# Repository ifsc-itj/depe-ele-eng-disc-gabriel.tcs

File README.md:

# template-discente-10-fases
Template para repositório de alunos para cursos com 10 fases

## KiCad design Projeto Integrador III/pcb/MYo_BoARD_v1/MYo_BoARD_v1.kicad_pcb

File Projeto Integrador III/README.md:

# MYo_BoARD
---
<p style="text-align: justify;">
Projeto de uma placa de aquisição de sinais biomédicos  de 3 canais desenvolvida na disciplina de Projeto Integrador III do curso de Engenharia Elétrica do IFSC-Itajaí.
</p>

---
## Sumário

- [MYo\_BoARD](#myo_board)
  - [Sumário](#sumário)
  - [Introdução](#introdução)
    - [Os biossinais](#os-biossinais)
    - [Fluxograma do sistema](#fluxograma-do-sistema)
  - [Ensaio de frequência nos amplificadores - *AC Sweep*](#ensaio-de-frequência-nos-amplificadores---ac-sweep)
  - [Projeto do circuito de aquisição](#projeto-do-circuito-de-aquisição)
    - [Filtro Notch](#filtro-notch)
    - [Pré-amplificação](#pré-amplificação)
    - [Filtro passa-baixas](#filtro-passa-baixas)
    - [Ganho e *Offset*](#ganho-e-offset)
  - [Circuito Completo (v2)](#circuito-completo-v2)
  - [ESP-32 S3 - Características de Interesse](#esp-32-s3---características-de-interesse)
  - [Plataforma de Aquisição (MYo\_GRaPH)](#plataforma-de-aquisição-myo_graph)
    - [Interface Inicial](#interface-inicial)
    - [Interface Final](#interface-final)

---
## Introdução
### Os biossinais

<p style="text-align: justify;">
Os biossinais são manifestações elétricas geradas pela atividade fisiológica dos tecidos e órgãos do corpo humano. Entre os mais estudados e aplicados em sistemas de aquisição e análise estão o eletroencefalograma (EEG), o eletrocardiograma (ECG) e o eletromiograma (EMG). Esses sinais carregam informações valiosas sobre o funcionamento do sistema nervoso, do coração e dos músculos esqueléticos, sendo amplamente utilizados em diagnósticos médicos, controle de próteses, interfaces cérebro-máquina e em pesquisas na área biomédica.
</p>

<p style="text-align: justify;">
O sinal de EEG reflete a atividade elétrica cerebral, caracterizado por amplitudes muito baixas (na ordem de microvolts) e frequências relativamente baixas (até cerca de 100 Hz). Devido à sua suscetibilidade a ruídos e interferências, sua captação exige alto grau de amplificação e filtragem. É amplamente utilizado em estudos de sono, epilepsia e monitoramento do estado cognitivo.
</p>

<p style="text-align: justify;">
Já o ECG registra a atividade elétrica do coração durante o ciclo cardíaco. Suas amplitudes são mais elevadas do que as do EEG e suas frequências se concentram nas faixas de até 150 Hz. O ECG é essencial no diagnóstico de arritmias, infartos e outras condições cardíacas, sendo um dos exames biomédicos mais comuns.
</p>

<p style="text-align: justify;">
O EMG, por sua vez, capta a atividade elétrica dos músculos esqueléticos, resultante da ativação das fibras musculares pelo sistema nervoso. O sinal mioelétrico é caracterizado por amplitudes maiores (até milivolts) e uma banda de frequência que pode variar entre 20 Hz e 5000 Hz, dependendo do tipo de contração muscular e do músculo analisado. Este sinal é de particular interesse em aplicações de reabilitação, controle de próteses ativas e em sistemas de interação homem-máquina.
</p>

<table>
<thead>
  <tr>
    <th style="text-align:center">Biossinal</th>
    <th style="text-align:center">Faixa de Frequência (Hz)</th>
    <th style="text-align:center">Amplitude Típica</th>
  </tr>
</thead>
<tbody>
  <tr>
    <td style="text-align:center">EEG</td>
    <td style="text-align:center">0,5 – 100</td>
    <td style="text-align:center">10 – 100 µV</td>
  </tr>
  <tr>
    <td style="text-align:center">ECG</td>
    <td style="text-align:center">0,05 – 150</td>
    <td style="text-align:center">0,5 – 4 mV</td>
  </tr>
  <tr>
    <td style="text-align:center">EMG</td>
    <td style="text-align:center">20 – 5000 (típico até 500)</td>
    <td style="text-align:center">50 µV – 5 mV</td>
  </tr>
</tbody>
</table>

### Fluxograma do sistema

O sistema foi desenvolvido conforme os fluxogramas a seguir.

| <br><em>Fluxograma da versão com filtro Notch e alimentação simétrica (v1).</em> |
|:--:|

| <br><em>Fluxograma da versão sem filtro Notch e alimentação assimétrica (v2).</em> |
|:--:|

## Ensaio de frequência nos amplificadores - *AC Sweep*

<p style="text-align: justify;">
A fim de verificar a resposta em frequência dos amplificadores de instrumentação, realizou-se um ensaio que consiste em variar a frequência do sinal de entrada e medir o sinal na saída do amplificador. Dessa maneira, é possível obter um gráfico que descreve a variação do ganho em função do aumento da frequência a partir dos valores de entrada e saída medidos. O circuito para ensaio dos amplificadores foram montados conforme recomendação do <em>datasheet</em> de cada um deles (vide Figura 1). Tanto o INA128 e o AD623 possuem a mesma configuração de pinos e, portanto, utilizou-se o mesmo circuito para ambos, diferenciando apenas no valor dos resistores de ganho. A resposta de cada amplificador consta na Figura 2. Os equipamentos utilizados para esse ensaio foram: osciloscópio digital e gerador de funções, ambos disponibilizados pelo <em>campus</em>.
</p>

| <br><em>Figura 1 – Circuito AC Sweep</em> |
|:--:|

| <br><em>Figura 2 – Resposta em frequência dos amplificadores</em> |
|:--:|

## Projeto do circuito de aquisição
### Filtro Notch

<p style="text-align: justify;">
O primeiro estágio do circuito consiste em um filtro que remova sinais de frequência de 60 Hz a fim de evitar interferências ruidosas oriundas da rede. Para tal filtro, utilizou-se a topologia Duplo-T, a qual permite selecionar a frequência central e o fator de qualidade de forma independente. O circuito obtido e a sua respectiva resposta constam nas Figuras 3 e 4, respectivamente. A Figura 5 mostra a resposta do circuito já montado e testado em bancada.
</p>

| <br><em>Figura 3 – Circuito do Filtro Notch</em> |
|:--:|

| <br><em>Figura 4 – Resposta em frequência do filtro Notch (Simulado)</em> |
|:--:|

| <br><em>Figura 5 – Resposta em frequência do filtro Notch (Real)</em> |
|:--:|

### Pré-amplificação

<p style="text-align: justify;">
O segundo estágio consiste em um amplificador de instrumentação que mitiga o ruído de modo comum (<em>CMRR</em>) do sinal diferencial. Portanto, o ganho nesse estágio pode ser mais baixo, optando-se, então, por dar um maior ganho em estágios posteriores. Devido a banda de passagem do AD623AN ser mais linear que a do INA128P, optou-se por utilizá-lo no circuito dessa etapa. O circuito utilizado nessa etapa é o mesmo da Figura 1, o qual é o recomendado pelo fabricante no <em>datasheet</em>
</p>

### Filtro passa-baixas

<p style="text-align: justify;">
O terceiro estágio consiste em um filtro passa-baixas de segunda ordem, topologia Sallen-Key. Esse filtro possui frequência de corte em 1 kHz. O circuito utilizado foi o da Figura 6. A Figura 7 Mostra a resposta em frequência obtida para o circuito em simulação.
</p>

| <br><em>Figura 6 – Circuito do filtro passa-baixas</em> |
|:--:|

| <br><em>Figura 7 – Resposta em frequência do filtro Passa-baixas (Simulado)</em> |
|:--:|

### Ganho e *Offset*

<p style="text-align: justify;">
Nessa etapa, o sinal é condicionado dentro dos limites de operação do ESP-32 S3. É dado um ganho variável de 1 à 201 e um deslocamento de tensão DC de, aproximadamente, 1,65 V.
</p>

## Circuito Completo (v2)

<p style="text-align: justify;">
Dado às necessidades de condicionamento do sinal serem cruciais à esse projeto e à algumas dificuldades encontradas durante a montagem e testes do circuito em <em>protoboard</em>, optou-se por não utilizar o filtro Notch (Duplo-T) devido ao mesmo exigir uma alimentaçã simétrica, o que trouxe dificuldades na montagem e teste em bancada, inviabilizando, então, a validação de seu funcionamento. Com isso, utilizou-se uma configuração já conhecida e validada em projetos anteriores com alimentação simétrica, mas sem o filtro analógico Notch. O esquemátio do circuito completo e o layout da placa de circuito impresso (PCI) constam nas figuras abaixo.
</p>

| <br><em>Circuito Completo (v2)</em> |
|:--:|

| <br><em>Visão Superior da PCI</em> |
|:--:|

| <br><em>Visão Inferior da PCI</em> |
|:--:|

<p style="text-align: justify;">
A ideia final do projeto é que as placas sejam módulos independentes que podem ser concatenados, formando uma rede de aquisição de multiplos canais, a depender da aplicação e da capacidade do microcontrolador adotado para o projeto. No presente projeto a proposta são 3 canais de aquisição e a utilização do ESP-32 S3.
</p>

## ESP-32 S3 - Características de Interesse

| Parâmetro                          | Valor                                                                                                             |
| ---------------------------------- | ----------------------------------------------------------------------------------------------------------------- |
| **Canalização ADC**                | 2 × SAR ADC de 12 bits, até 20 canais (ADC1\_CH0…CH9 disponíveis com Wi-Fi; ADC2 indisponível quando Wi-Fi ativo) |
| **Taxa máxima de amostragem**      | 100 kSPS (100 000 samples/s)                                                                                      |
| **Taxa efetiva por canal**         | ≈ 33 kSPS por canal (100 kSPS ÷ 3)                                                                                |
| **Tempo de conversão**             | ≈ 10 µs (1 / 100 kSPS)                                                                                            |
| **Faixa de tensão de entrada**     | –0.3 … +3.6 V                                                                                                     |
| **Memória interna**                | ROM: 384 KB<br>SRAM: 512 KB<br>RTC SRAM: 16 KB                                                                    |
| **Recomendação de desacoplamento** | 100 nF no pino ADC para redução de ruído                                                                          |
| **Suporte a DMA**                  | Sim, via GDMA (periférico ADC mapeado com DMA)                                                                    |
| **Restrições com Wi-Fi**           | ADC2 indisponível quando Wi-Fi ativo (usar ADC1 para amostragem contínua)                                    |

## Plataforma de Aquisição (MYo_GRaPH)

### Interface Inicial
<p style="text-align: justify;">
Para o desenvolvimento da interface, foi utilizado a linguagem Python. A dependências utilizadas constam no arquivo <code>MYo_GRaPH\v1\requirements.txt</code>. Crie um ambiente de virtual e instale as dependências utilizando o gerenciador de pacotes: <code>pip install -r requirements.txt</code>.

As telas da interface inicial constam nas figuras abaixo, onde:
</p>

| Botão    | Função                                                           |
|----------|------------------------------------------------------------------|
| Start    | Inicia a leitura via porta serial                                |
| Stop     | Interrompe a leitura via porta serial                            |
| Duration | Determina o tempo de aquisição do sinal para gravação            |
| Record   | Inicia a gravação dos 3 canais e salva em arquivos *.wav* distintos |

| <br><em>Janela principal</em> |
|:--:|

| <br><em>Janela principal (Start ativado)</em> |
|:--:|

| <br><em>Janela de visualização de sinal gravado (sinal simulado)</em> |
|:--:|

### Interface Final
<p style="text-align: justify;">
Na interface final, foram adicionadas as funções de abrir arquivos <em>.wav</em> por meio do menu <code>File > Open File</code>; remover o nível DC do sinal; e selecionar a quantidade de canais a serem exibidos. Adicionou-se também a aquisição e conversão do sinal com ESP-32 S3 e amostragem do sinal via porta Serial com Python.
</p>

<p style="text-align: justify;">
A tela da interface final consta na figura abaixo, onde:
</p>

| Botão    | Função                                                           |
|----------|------------------------------------------------------------------|
| Start    | Inicia a leitura via porta serial                                |
| Stop     | Interrompe a leitura via porta serial                            |
| Duration | Determina o tempo de aquisição do sinal para gravação (não implementado)            |
| Record   | Inicia a gravação dos 3 canais e salva em arquivos *.wav* distintos (não implementado) |
| Remove DC   | Quando selecionado, remove o nivel DC do sinal |
| Canais   | Seleciona a quantidade de canais para leitura |
| Dark Mode/Light Mode   | Alterna entre modo claro e escuro na exibição do gráfico |

| <br><em>Janela de visualização de sinal em "tempo real" (sinal oriundo do gerador de funções)</em> |
|:--:|

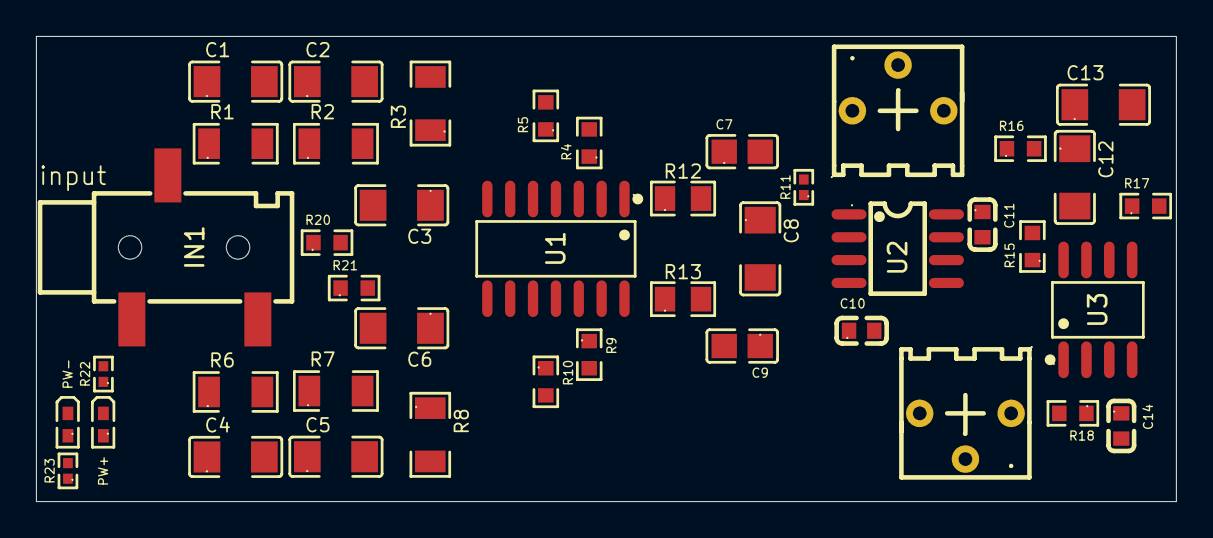
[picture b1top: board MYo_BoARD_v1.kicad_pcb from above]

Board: 2 copper layers, 63.3 x 25.8 mm, 43 parts (0 on the bottom side), 32 nets, no tracks yet.

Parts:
C1, C2, C4, C5, C13: 20n; C1206
C3, C6: 39n; C1206
C7, C9: 1n; C0805
C8: 47n; C1206
C10, C11, C14: 10u; C0603
C12: 10n; C1206
D1: PW+; LED0402-R-RD_RED
D2: PW-; LED0402-R-RD_RED
IN1: AUDIO-SMD_PJ-320B
R1, R2, R6, R7: 133k; R1206
R3, R8: 66.5k; R1206
R4, R9, R17, R18: 100R; R0603
R5, R10: 3.9k; R0603
R11: 5.23k; R0402
R12, R13: 4.02k; R0805
R14, R19: 3362P-1-203LF; RES-ADJ-TH_3362P
R15, R16, R20, R21: 10k; R0603
R22, R23: 330R; R0402
U1: TLC2274AIDR; SOIC-14_L8.7-W3.9-P1.27-LS6.0-BL
U2: AD623ARZ-R7; SOIC-8_L5.0-W4.0-P1.27-LS6.0-BL
U3: TLC2272AIDR; SOIC-8_L4.9-W3.9-P1.27-LS6.0-BL

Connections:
unnamed: C1.1, IN1.2, R1.1
unnamed: C1.2, C2.1, R3.2
unnamed: C3.2, R1.2, R2.1
unnamed: C4.1, IN1.3, R6.1
unnamed: C4.2, C5.1, R8.2
unnamed: C6.2, R6.2, R7.1
unnamed: C13.1, R15.2, R16.1
unnamed: D1.2 (A), R22.2
unnamed: D2.1 (K), R23.2
unnamed: R11.2, R14.1
unnamed: R18.2, R19.1
unnamed: C2.2, R2.2, U1.3 (IN1+)
unnamed: R4.1, R12.1, U1.1 (OUT1), U1.2 (IN1-)
unnamed: R4.2, R5.1, U1.5 (IN2+)
unnamed: C3.1, R3.1, U1.6 (IN2-), U1.7 (OUT2)
unnamed: C5.2, R7.2, U1.10 (IN3+)
unnamed: R9.1, R13.1, U1.8 (OUT3), U1.9 (IN3-)
unnamed: R9.2, R10.1, U1.12 (IN4+)
unnamed: C6.1, R8.1, U1.13 (IN4-), U1.14 (OUT4)
unnamed: C8.2, C9.1, R13.2, U2.3 (+IN)
unnamed: R14.2, U2.8 (+RG)
unnamed: C7.2, C8.1, R12.2, U2.2 (-IN)
unnamed: R11.1, U2.1 (-RG)
unnamed: R15.1, U2.6 (OUTPUT)
unnamed: C13.2, R17.1, U3.5 (IN2+), U3.7 (OUT2)
unnamed: C12.1, R16.2, U3.6 (IN2-)
unnamed: R17.2, R18.1, U3.2 (IN1-)
unnamed: R19.2, U3.1 (OUT1)
gnd: C7.1, C9.2, C10.2, C11.1, C12.2, C14.2, D1.1 (K), D2.2 (A), IN1.1, R5.2, R10.2, R21.2, U2.5 (REF)
v+: C11.2, R20.1, R22.1, U1.4 (VDD+), U2.7 (+VS), U3.8 (VDD+)
v-: C10.1, R23.1, U1.11 (VDD-), U2.4 (-VS), U3.4 (VDD-GND)
vcc/2: C14.1, R20.2, R21.1, U3.3 (IN1+)

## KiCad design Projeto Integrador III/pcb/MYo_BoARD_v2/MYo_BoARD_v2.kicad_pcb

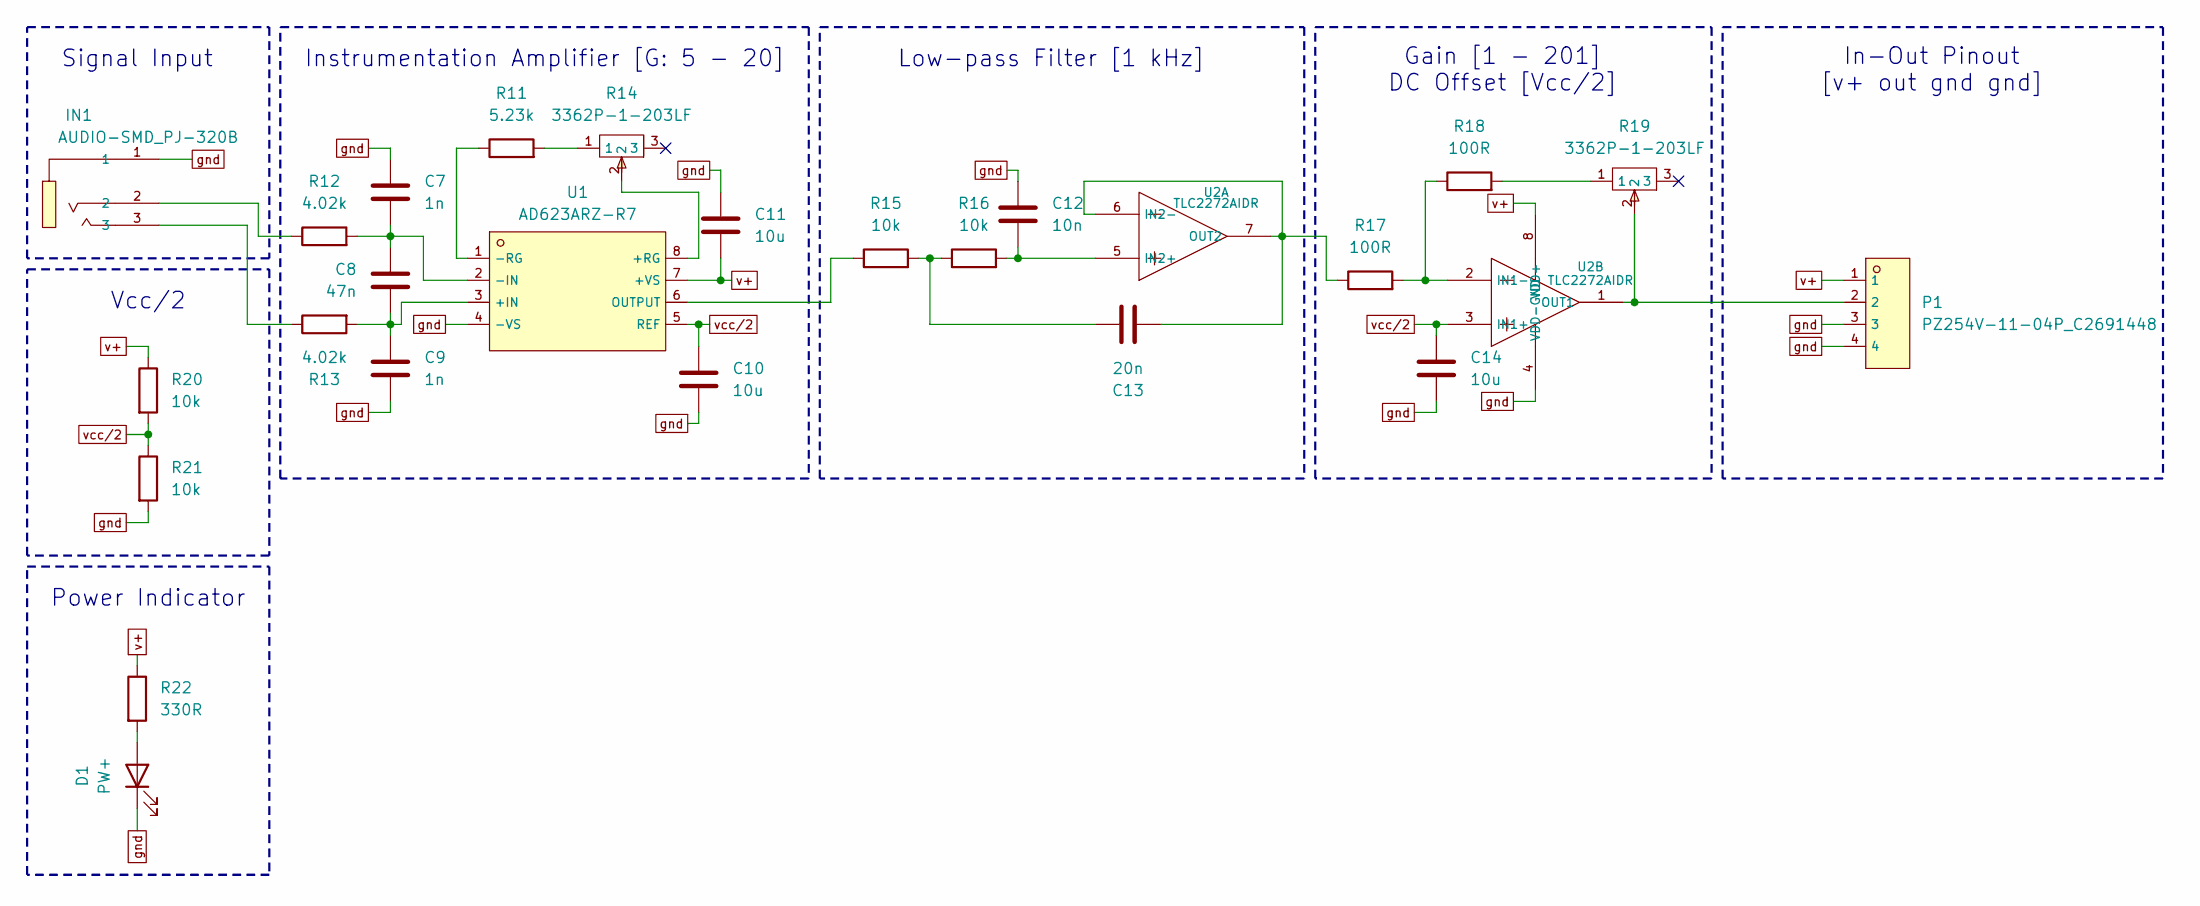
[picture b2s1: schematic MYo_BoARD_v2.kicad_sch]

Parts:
C7, C9: 1n; C0805; LCSC C1791
C8: 47n; C1206; LCSC C21812
C10, C11, C14: 10u; C0603; LCSC C77044
C12: 10n; C1206; LCSC C97928
C13: 20n; C1206; LCSC C172741
D1: PW+; LED0402-R-RD_RED; LCSC C136765
IN1: AUDIO-SMD_PJ-320B; LCSC C18594
P1: PZ254V-11-04P_C2691448; HDR-TH_4P-P2.54-V-M; LCSC C2691448
R11: 5.23k; R0402; LCSC C241138
R12, R13: 4.02k; R0805; LCSC C844212
R14, R19: 3362P-1-203LF; RES-ADJ-TH_3362P; LCSC C81263
R15, R16, R20, R21: 10k; R0603; LCSC C845630
R17, R18: 100R; R0603; LCSC C3995643
R22: 330R; R0402; LCSC C427206
U1: AD623ARZ-R7; SOIC-8_L5.0-W4.0-P1.27-LS6.0-BL; LCSC C9676
U2: TLC2272AIDR; SOIC-8_L4.9-W3.9-P1.27-LS6.0-BL; LCSC C146678

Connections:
unnamed: C13.1, R15.2, R16.1
unnamed: D1.2 (A), R22.2
unnamed: IN1.2, R12.1
unnamed: IN1.3, R13.1
unnamed: R11.2, R14.1
unnamed: R18.2, R19.1
unnamed: C8.2, C9.1, R13.2, U1.3 (+IN)
unnamed: R14.2, U1.8 (+RG)
unnamed: C7.2, C8.1, R12.2, U1.2 (-IN)
unnamed: R11.1, U1.1 (-RG)
unnamed: R15.1, U1.6 (OUTPUT)
unnamed: C12.2, R16.2, U2.5 (IN2+)
unnamed: C13.2, R17.1, U2.6 (IN2-), U2.7 (OUT2)
unnamed: R17.2, R18.1, U2.2 (IN1-)
unnamed: P1.2, R19.2, U2.1 (OUT1)
gnd: C7.1, C9.2, C10.2, C11.1, C12.1, C14.2, D1.1 (K), IN1.1, P1.3, P1.4, R21.2, U1.4 (-VS), U2.4 (VDD-GND)
v+: C11.2, P1.1, R20.1, R22.1, U1.7 (+VS), U2.8 (VDD+)
vcc/2: C10.1, C14.1, R20.2, R21.1, U1.5 (REF), U2.3 (IN1+)

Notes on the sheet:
In-Out Pinout [v+ out gnd gnd]
Instrumentation Amplifier [G: 5 - 20]
Low-pass Filter [1 kHz]
Power Indicator
Signal Input
Vcc/2
Gain [1 - 201] DC Offset [Vcc/2]

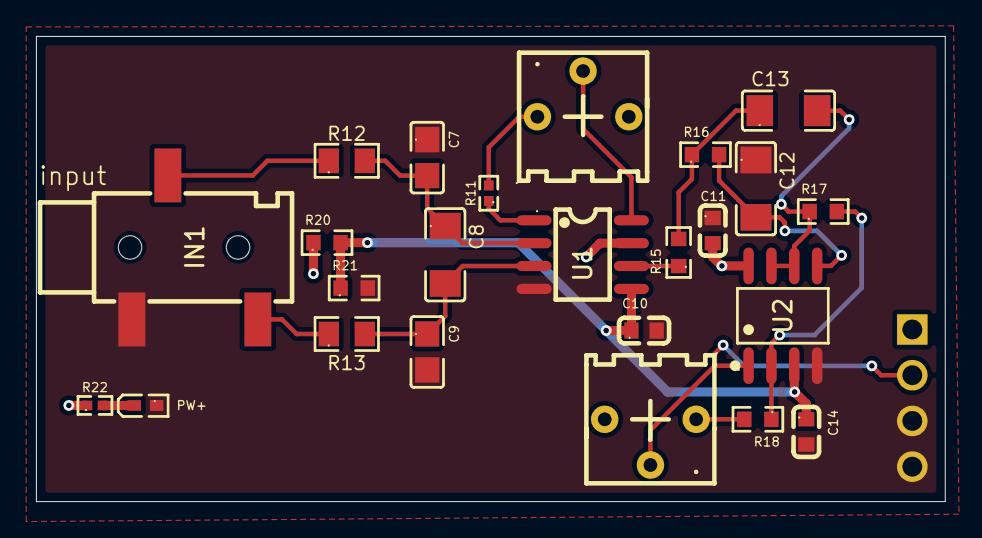
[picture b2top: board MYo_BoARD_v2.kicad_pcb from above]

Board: 2 copper layers, 50.5 x 25.8 mm, 25 parts (1 on the bottom side), 18 nets.

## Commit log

2025-06-12 Introdução e Simulações
2025-07-12 PCI Finalizada V2
2025-07-12 Modificação no README.md
2025-07-16 Interface Inicial
2025-07-18 Atualização final de documentação e adição do .gitignore
2025-07-22 Atualização dos arquivos .gitignore
2025-08-12 Comunicação OPC UA Python Server
2025-08-12 Monografia v0: modelo
